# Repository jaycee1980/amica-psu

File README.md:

# amica-psu
A USB PD power supply for Amiga computers

## PLEASE NOTE !!
This project is not yet finished ! The hardware is complete, but the firmware for the STM8 microcontroller is not finished. I decided to upload the project anyway rather than the work going to waste.
Hopefully if I can get my brain in working order, I will finish it.

## Does it even work?
The DC-DC conversion stuff works... see [here](https://youtu.be/czb_NR_QA5E) and [here](https://youtu.be/kD3LM56WTJc) to see it working
The HUSB238A works as it is being used in that second video on a breakout board. I have controlled the HUSB238 successfully using an Arduino.

## License
The hardware is licensed under the [Creative Commons non-commercial license](https://creativecommons.org/licenses/by-nc/4.0/)

The software is licensed under the [Zlib license](https://opensource.org/license/Zlib)

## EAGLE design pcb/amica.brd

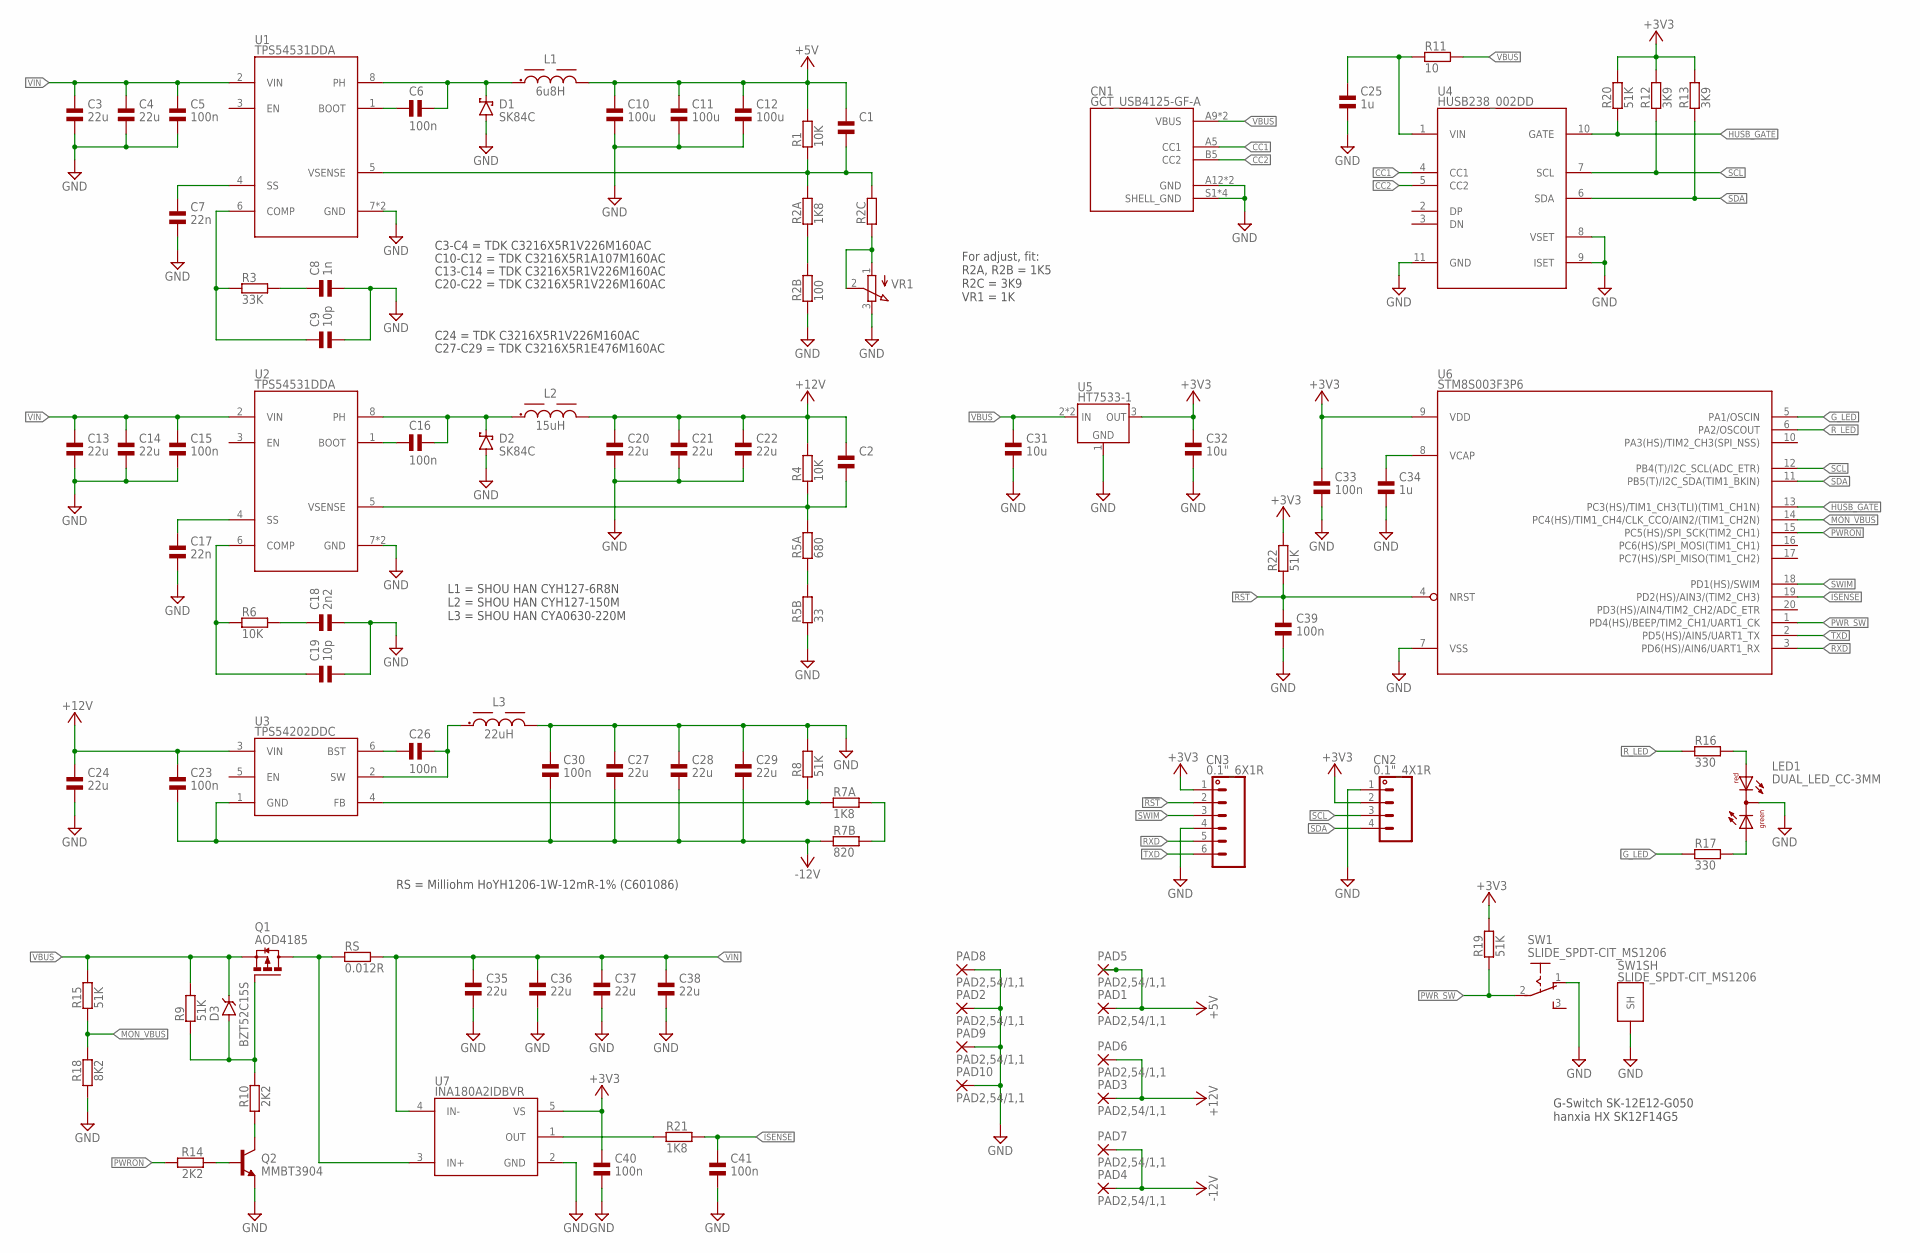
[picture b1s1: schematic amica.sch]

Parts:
C1, C2: CAP_NPOL-0603; 0603
C3, C4, C13, C14, C20, C21, C22, C24, C27, C28, C29, C35, C36, C37, C38: 22u; 1206; LCSC_PART C12891
C5, C6, C15, C16, C23, C26, C30, C33, C39, C40, C41: 100n; 0603; LCSC_PART C14663
C7, C17: 22n; 0603; LCSC_PART C21122
C8: 1n; 0603; LCSC_PART C1588
C9, C19: 10p; 0603; LCSC_PART C1634
C10, C11, C12: 100u; 1206; LCSC_PART C15008
C18: 2n2; 0603; LCSC_PART C1604
C25, C34: 1u; 0603; LCSC_PART C15849
C31: 10u; 0805; LCSC_PART C15850
C32: 10u; 0603; LCSC_PART C19702
CN1: GCT_USB4125-GF-A; GCT_USB4125-GF-A-0190_REVA2; LCSC_PART C18357552
CN2: 0.1"_4X1R; 0.1"_4X1-ROUND
CN3: 0.1"_6X1R; 0.1"_6X1-ROUND
D1, D2: SK84C; SMC; LCSC_PART C28646293
D3: BZT52C15S; SOD323F; LCSC_PART C19077448
L1: 6u8H; SHOUHAN_CYH125; LCSC_PART C2929498
L2: 15uH; SHOUHAN_CYH125; LCSC_PART C2929500
L3: 22uH; SHOUHAN_CYA0630; LCSC_PART C5189960
LED1: DUAL_LED_CC-3MM; DUOLED-3MM
PAD1, PAD2, PAD3, PAD4, PAD5, PAD6, PAD7, PAD8, PAD9, PAD10: PAD2,54/1,1; 2,54/1,1
Q1: AOD4185; DPAK; LCSC_PART C400894
Q2: MMBT3904; SOT23; LCSC_PART C7420353
R1, R4, R6: 10K; 0603; LCSC_PART C25804
R2A, R7A, R21: 1K8; 0603; LCSC_PART C4177
R2B: 100; 0603; LCSC_PART C22775
R2C: RES-SMD_0603; 0603
R3: 33K; 0603; LCSC_PART C4216
R5A: 680; 0603; LCSC_PART C23228
R5B: 33; 0603; LCSC_PART C23140
R7B: 820; 0603; LCSC_PART C23253
R8, R9, R15, R19, R20, R22: 51K; 0603; LCSC_PART C23196
R10, R14: 2K2; 0603; LCSC_PART C4190
R11: 10; 0805; LCSC_PART C17415
R12, R13: 3K9; 0603; LCSC_PART C23018
R16, R17: 330; 0603; LCSC_PART C23138
R18: 8K2; 0603; LCSC_PART C25981
RS: 0.012R; 1206; LCSC_PART C601086
SW1: SLIDE_SPDT-CIT_MS1206; CIT_MS1206; LCSC_PART C2848870
U1, U2: TPS54531DDA; SO08-EP; LCSC_PART C50605
U3: TPS54202DDC; SOT23-6; LCSC_PART C191884
U4: HUSB238_002DD; DFN10-3X3; LCSC_PART C7471904
U5: HT7533-1; SOT89; LCSC_PART C14289
U6: STM8S003F3P6; TSSOP20; LCSC_PART C52717
U7: INA180A2IDBVR; SOT23-5; LCSC_PART C192764
VR1: TRIMMER-BOURNS_3362P; TRIM_3362P-1

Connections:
5V_BST: C6.1, U1.1 (BOOT)
5V_COMP: C9.1, R3.1, U1.6 (COMP)
5V_FB: C1.2, R1.1, R2A.2, R2C.2, U1.5 (VSENSE)
5V_SS: C7.1, U1.4 (SS)
5V_SW: C6.2, D1.K (C), L1.P$1 (1), U1.8 (PH)
12V_BST: C16.1, U2.1 (BOOT)
12V_COMP: C19.1, R6.1, U2.6 (COMP)
12V_FB: C2.2, R4.1, R5A.2, U2.5 (VSENSE)
12V_SS: C17.1, U2.4 (SS)
12V_SW: C16.2, D2.K (C), L2.P$1 (1), U2.8 (PH)
!RST: C39.1, CN3.2, R22.1, U6.4 (NRST)
+3V3: C32.1, C33.1, C40.1, CN2.2, CN3.1, R12.2, R13.2, R19.2, R20.2, R22.2, U5.3 (OUT), U6.9 (VDD), U7.5 (VS)
+5V: C1.1, C10.1, C11.1, C12.1, L1.P$2 (2), PAD1.1, PAD5.1, R1.2
+12V: C2.1, C20.1, C21.1, C22.1, C23.1, C24.1, L2.P$2 (2), PAD3.1, PAD6.1, R4.2, U3.3 (VIN)
-12V: C23.2, C27.2, C28.2, C29.2, C30.2, PAD4.1, PAD7.1, R7B.1, U3.1 (GND)
-12V_BST: C26.1, U3.6 (BST)
-12V_FB: R7A.1, R8.1, U3.4 (FB)
-12V_SW: C26.2, L3.P$1 (1), U3.2 (SW)
CC1: CN1.A5 (CC1), U4.4 (CC1)
CC2: CN1.B5 (CC2), U4.5 (CC2)
GND: C3.2, C4.2, C5.2, C7.2, C8.2, C9.2, C10.2, C11.2, C12.2, C13.2, C14.2, C15.2, C17.2, C18.2, C19.2, C20.2, C21.2, C22.2, C24.2, C25.2, C27.1, C28.1, C29.1, C30.1, C31.2, C32.2, C33.2, C34.2, C35.2, C36.2, C37.2, C38.2, C39.2, C40.2, C41.2, CN1.A12 (GND), CN1.B12 (GND), CN1.S1 (SHELL_GND), CN1.S2 (SHELL_GND), CN1.S3 (SHELL_GND), CN1.S4 (SHELL_GND), CN2.1, CN3.4, D1.A, D2.A, L3.P$2 (2), LED1.COM (C), PAD2.1, PAD8.1, PAD9.1, PAD10.1, Q2.2 (E), R2B.1, R5B.1, R8.2, R18.2, SW1.1 (O), SW1.GND@1 (SH), SW1.GND@2 (SH), U1.7 (GND), U1.PAD (GND), U2.7 (GND), U2.PAD (GND), U4.8 (VSET), U4.9 (ISET), U4.11 (GND), U5.1 (GND), U6.7 (VSS), U7.2 (GND), VR1.3 (CW)
G_LED: R17.1, U6.5 (PA1/OSCIN)
HUSB_GATE: R20.1, U4.10 (GATE), U6.13 (PC3(HS)/TIM1_CH3(TLI)(TIM1_CH1N))
HUSB_VIN: C25.1, R11.1, U4.1 (VIN)
ISENSE: C41.1, R21.2, U6.19 (PD2(HS)/AIN3/(TIM2_CH3))
MON_VBUS: R15.1, R18.1, U6.14 (PC4(HS)/TIM1_CH4/CLK_CCO/AIN2/(TIM1_CH2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)
unnamed: D3.A, Q1.1 (G), R9.1, R10.1
unnamed: LED1.2 (AR), R16.2
unnamed: R2A.1, R2B.2
unnamed: R2C.1, VR1.1 (CCW), VR1.2 (W)
unnamed: C18.1, R6.2
unnamed: C34.1, U6.8 (VCAP)
unnamed: LED1.1 (AG), R17.2
unnamed: Q2.1 (B), R14.1
unnamed: R5A.1, R5B.2
unnamed: C8.1, R3.2
unnamed: R21.1, U7.1 (OUT)
unnamed: R7A.2, R7B.2
unnamed: Q2.3 (C), R10.2
PWRON: R14.2, U6.15 (PC5(HS)/SPI_SCK(TIM2_CH1))
PWR_SW: R19.1, SW1.2, U6.1 (PD4(HS)/BEEP/TIM2_CH1/UART1_CK)
RXD: CN3.5, U6.3 (PD6(HS)/AIN6/UART1_RX)
R_LED: R16.1, U6.6 (PA2/OSCOUT)
SCL: CN2.3, R12.1, U4.7 (SCL), U6.12 (PB4(T)/I2C_SCL(ADC_ETR))
SDA: CN2.4, R13.1, U4.6 (SDA), U6.11 (PB5(T)/I2C_SDA(TIM1_BKIN))
SWIM: CN3.3, U6.18 (PD1(HS)/SWIM)
TXD: CN3.6, U6.2 (PD5(HS)/AIN5/UART1_TX)
VBUS: C31.1, CN1.A9 (VBUS), CN1.B9 (VBUS), D3.C, Q1.3 (S), R9.2, R11.2, R15.2, U5.2 (IN), U5.2@1 (IN)
VBUS_SW: Q1.4 (D), RS.1, U7.3 (IN+)
VIN: C3.1, C4.1, C5.1, C13.1, C14.1, C15.1, C35.1, C36.1, C37.1, C38.1, RS.2, U1.2 (VIN), U2.2 (VIN), U7.4 (IN-)

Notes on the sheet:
C20-C22 = TDK C3216X5R1V226M160AC
C10-C12 = TDK C3216X5R1A107M160AC
C13-C14 = TDK C3216X5R1V226M160AC
C3-C4 = TDK C3216X5R1V226M160AC
C24 = TDK C3216X5R1V226M160AC
C27-C29 = TDK C3216X5R1E476M160AC
G-Switch SK-12E12-G050 hanxia HX SK12F14G5
For adjust, fit: R2A, R2B = 1K5 R2C = 3K9 VR1 = 1K
L1 = SHOU HAN CYH127-6R8N L2 = SHOU HAN CYH127-150M L3 = SHOU HAN CYA0630-220M
RS = Milliohm HoYH1206-1W-12mR-1% (C601086)

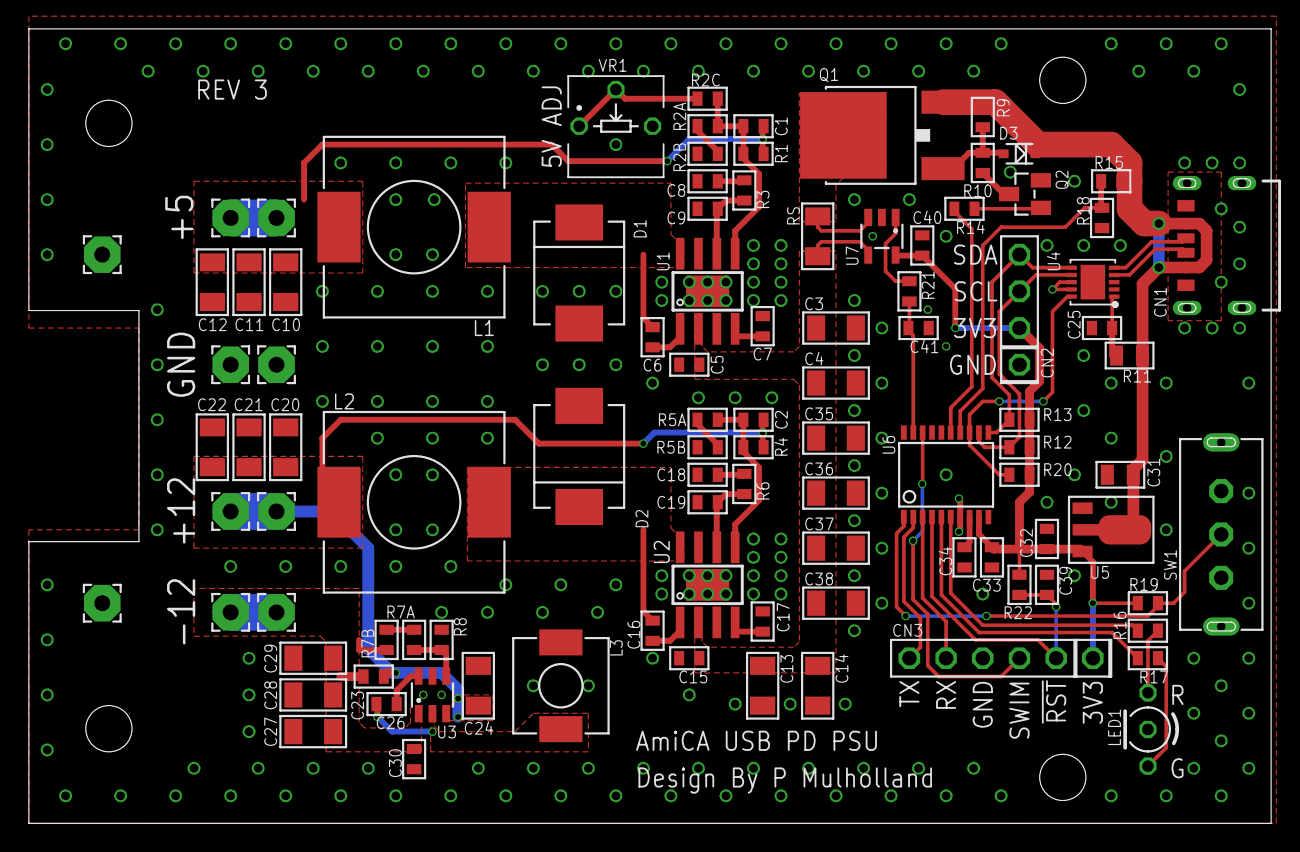
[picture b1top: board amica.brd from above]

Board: 2 copper layers, 86.0 x 55.0 mm, 99 parts (0 on the bottom side), 50 nets.

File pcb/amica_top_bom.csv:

Comment,Designator,Footprint,LCSC Part #
0.012R,RS,1206,C601086
1K8,R2A R7A R21,0603,C4177
1n,C8,0603,C1588
1u,C25 C34,0603,C15849
2K2,R10 R14,0603,C4190
2n2,C18,0603,C1604
3K9,R12 R13,0603,C23018
6u8H,L1,SHOUHAN_CYH125,C2929498
8K2,R18,0603,C25981
10,R11,0805,C17415
10K,R1 R4 R6,0603,C25804
10p,C9 C19,0603,C1634
10u,C31,0805,C15850
10u,C32,0603,C19702
15uH,L2,SHOUHAN_CYH125,C2929500
22n,C7 C17,0603,C21122
22u,C3 C4 C13 C14 C20 C21 C22 C24 C27 C28 C29 C35 C36 C37 C38,1206,C12891
22uH,L3,SHOUHAN_CYA0630,C5189960
33,R5B,0603,C23140
33K,R3,0603,C4216
51K,R8 R9 R15 R19 R20 R22,0603,C23196
100,R2B,0603,C22775
100n,C5 C6 C15 C16 C23 C26 C30 C33 C39 C40 C41,0603,C14663
100u,C10 C11 C12,1206,C15008
330,R16 R17,0603,C23138
680,R5A,0603,C23228
820,R7B,0603,C23253
AOD4185,Q1,DPAK,C400894
BZT52C15S,D3,SOD323F,C19077448
GCT_USB4125-GF-A,CN1,GCT_USB4125-GF-A-0190_REVA2,C18357552
HT7533-1,U5,SOT89,C14289
HUSB238_002DD,U4,DFN10-3X3,C7471904
INA180A2IDBVR,U7,SOT23-5,C192764
MMBT3904,Q2,SOT23,C7420353
SK84C,D1 D2,SMC,C28646293
STM8S003F3P6,U6,TSSOP20,C52717
TPS54202DDC,U3,SOT23-6,C191884
TPS54531DDA,U1 U2,SO08-EP,C50605

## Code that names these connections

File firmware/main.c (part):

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/*
	STM8S003F3P6

	PA1		GPIO_Output, Green LED
	PA2		GPIO_Output, Red LED
	PA3		GPIO_Input, HUSB238 "GATE" pin state

	PB4		I2C_SCL
	PB5		I2C_SDA

	PC4		ADC_IN2 - VBUS voltage
	PC5		GPIO_Output, PWRON (high = on)

	PD1		SWIM
	PD2		ADC_IN3 - current sense 
	PD4		GPIO_Input, Power switch (low = on)
	PD5		UART1_TXD
	PD6		UART1_RXD
*/

// Bits to set in PA_ODR for the LEDs
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	// Configure GPIO pins

	// Port A
	// PA1 GPIO_Output, Green LED
	// PA2 GPIO_Output, Red LED
	// PA3 GPIO_Input, HUSB238 "GATE" pin state

	PA_DDR = 0b00000110;			// PA1-2 output, PA3 input
	PA_CR1 = 0b00000110;			// PA1-2 p-p out, PA3 no pullup
	PA_CR2 = 0b00001000;			// PA1-2 2MHz out, PA3 interrupt

	// Port B - PB4 and PB5 are used for I2C

	PB_DDR = 0;
	PB_CR1 = PB_CR2 = 0;

	// Port C
	// PC3 = unused
	// PC4 = ADC_IN2 - VBUS voltage
	// PC5 = GPIO_Output, output on (high = on)
	// PC6 = unused
	// PC7 = unused
	
	PC_DDR = 0b00100000;			// PC5 output, all others input
	PC_CR1 = 0b00100000;			// PC5 p-p out
	PC_CR2 = 0b00000000;			// PC5 2MHz out

	// Port D
	// PD1 = SWIM
	// PD2 = ADC_IN3 - current sense 
	// PD3 = not used
	// PD4 = GPIO_Input, Power switch (low = on)
	// PD5 = UART1_TXD
	// PD6 = UART1_RXD

	PD_DDR = 0b00000000;			// All inputs
	PD_CR1 = 0b00010010;			// PD4 pullup on, SWIM pullup on
	PD_CR2 = 0b00010000;			// PD4 interrupt on state change

	// ------------------------------------------------------------------------
	// Configure ADC
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
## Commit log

2025-11-25 Updated schematic to correct R7A/R7B resistor values
2025-11-25 Added EAGLE files
